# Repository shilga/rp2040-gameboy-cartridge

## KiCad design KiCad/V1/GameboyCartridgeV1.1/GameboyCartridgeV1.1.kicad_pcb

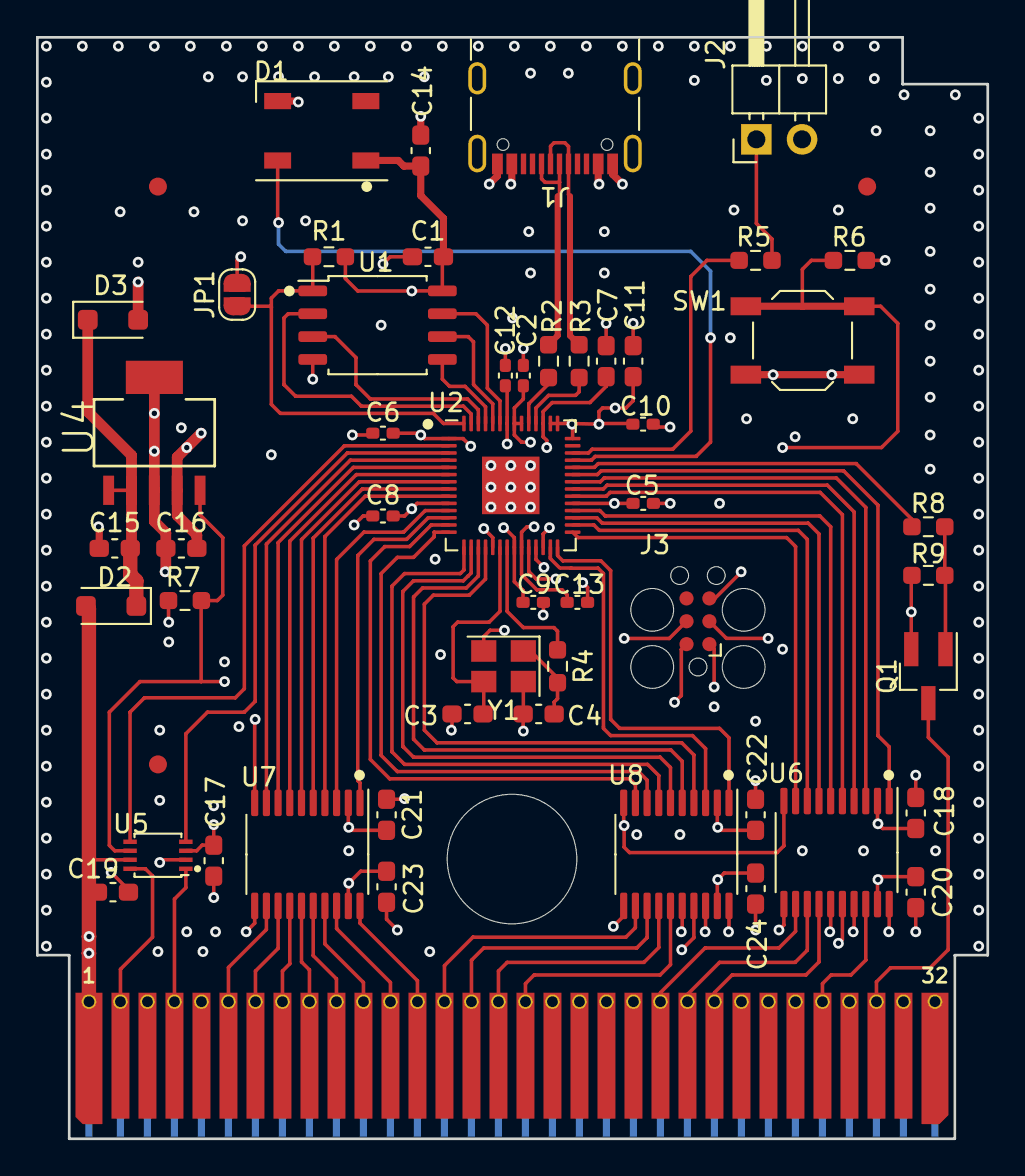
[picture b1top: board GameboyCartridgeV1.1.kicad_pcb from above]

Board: 4 copper layers, 52.8 x 61.2 mm, 54 parts (0 on the bottom side), 81 nets.

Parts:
C1, C14, C17, C18, C19, C20, C21, C22, C23, C24: 100nF; C_0603_1608Metric_Pad1.08x0.95mm_HandSolder
C2, C5, C6, C8, C9, C10, C12, C13: 100nF; C_0402_1005Metric_Pad0.74x0.62mm_HandSolder
C3, C4: 15pF; C_0603_1608Metric_Pad1.08x0.95mm_HandSolder
C7, C11: 2.2uF; C_0603_1608Metric_Pad1.08x0.95mm_HandSolder
C15: 4.7uF; C_0603_1608Metric_Pad1.08x0.95mm_HandSolder
C16: 10uF; C_0603_1608Metric_Pad1.08x0.95mm_HandSolder
D1: WS2812B; LED_WS2812B_PLCC4_5.0x5.0mm_P3.2mm
D2, D3: D_Schottky; D_SOD-123F
FID1, FID2, FID3: Fiducial; Fiducial_1mm_Mask2mm
J1: USB_C_Receptacle_USB2.0; USB_C_Receptacle_GCT_USB4105-xx-A_16P_TopMnt_Horizontal
J2: DBG_UART; PinHeader_1x02_P2.54mm_Horizontal
J3: Conn_01x06; Tag-Connect_TC2030-IDC-FP_2x03_P1.27mm_Vertical
JP1: USB_BOOT_SEL; SolderJumper-2_P1.3mm_Open_RoundedPad1.0x1.5mm
Q1: CJ2302; SOT-23_Handsoldering
R1, R6: 10k; R_0603_1608Metric_Pad0.98x0.95mm_HandSolder
R2, R3: 27R; R_0603_1608Metric_Pad0.98x0.95mm_HandSolder
R4, R8: 1k; R_0603_1608Metric_Pad0.98x0.95mm_HandSolder
R5: 10R; R_0603_1608Metric_Pad0.98x0.95mm_HandSolder
R7, R9: 470k; R_0603_1608Metric_Pad0.98x0.95mm_HandSolder
SW1: SW_Push; SW_SPST_TL3342
U1: W25Q128JVS; SOIC-8_5.23x5.23mm_P1.27mm
U2: RP2040; QFN-56-1EP_7x7mm_P0.4mm_EP3.2x3.2mm
U3: CartBus; GameBoy_Cartridge_EdgeConnector
U4: MCP1825T-3302E/DC; SOT230P700X180-6N
U5: TXB0102DCU; VSSOP-8_2.4x2.1mm_P0.5mm
U6, U7, U8: TXB0108PW; TSSOP-20_4.4x6.5mm_P0.65mm
Y1: 12MHz; Crystal_SMD_TXC_7M-4Pin_3.2x2.5mm

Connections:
+1V1: C7.2, C12.2, C13.2, U2.23 (DVDD), U2.45 (VREG_VOUT), U2.50 (DVDD)
+3V3: C1.2, C2.2, C5.2, C6.2, C8.2, C9.2, C10.2, C11.2, C14.2, C16.2, C17.2, C18.2, C21.2, C22.2, D1.1 (VDD), J3.1, R1.2, R6.2, R7.2, U1.8 (VCC), U2.1 (IOVDD), U2.10 (IOVDD), U2.22 (IOVDD), U2.33 (IOVDD), U2.42 (IOVDD), U2.43 (ADC_AVDD), U2.44 (VREG_IN), U2.48 (USB_VDD), U2.49 (IOVDD), U4.4 (VOUT), U5.3 (VCCA), U6.2 (VCCA), U7.2 (VCCA), U8.2 (VCCA)
+5V: C15.2, D2.1 (K), D3.1 (K), U4.1 (*SHDN), U4.2 (VIN)
ADDR_BUS0: U2.4 (GPIO2), U7.9 (A8)
ADDR_BUS1: U2.5 (GPIO3), U7.8 (A7)
ADDR_BUS2: U2.6 (GPIO4), U7.7 (A6)
ADDR_BUS3: U2.7 (GPIO5), U7.6 (A5)
ADDR_BUS4: U2.8 (GPIO6), U7.5 (A4)
ADDR_BUS5: U2.9 (GPIO7), U7.4 (A3)
ADDR_BUS6: U2.11 (GPIO8), U7.3 (A2)
ADDR_BUS7: U2.12 (GPIO9), U7.1 (A1)
ADDR_BUS8: U2.13 (GPIO10), U8.9 (A8)
ADDR_BUS9: U2.14 (GPIO11), U8.8 (A7)
ADDR_BUS10: U2.15 (GPIO12), U8.7 (A6)
ADDR_BUS11: U2.16 (GPIO13), U8.6 (A5)
ADDR_BUS12: U2.17 (GPIO14), U8.5 (A4)
ADDR_BUS13: U2.18 (GPIO15), U8.4 (A3)
ADDR_BUS14: U2.27 (GPIO16), U8.3 (A2)
ADDR_BUS15: U2.28 (GPIO17), U8.1 (A1)
BUS_CLK: U2.2 (GPIO0), U5.5 (A1)
BUS_RD: U2.3 (GPIO1), U5.4 (A2)
BUS_RST: R8.2, U2.38 (GPIO26_ADC0)
DATA_BUS0: U2.29 (GPIO18), U6.9 (A8)
DATA_BUS1: U2.30 (GPIO19), U6.8 (A7)
DATA_BUS2: U2.31 (GPIO20), U6.7 (A6)
DATA_BUS3: U2.32 (GPIO21), U6.6 (A5)
DATA_BUS4: U2.34 (GPIO22), U6.5 (A4)
DATA_BUS5: U2.35 (GPIO23), U6.4 (A3)
DATA_BUS6: U2.36 (GPIO24), U6.3 (A2)
DATA_BUS7: U2.37 (GPIO25), U6.1 (A1)
DEBUG_UART_TX: R5.1, U2.40 (GPIO28_ADC2)
GB_A0: U3.6 (A0), U7.12 (B8)
GB_A1: U3.7 (A1), U7.13 (B7)
GB_A2: U3.8 (A2), U7.14 (B6)
GB_A3: U3.9 (A3), U7.15 (B5)
GB_A4: U3.10 (A4), U7.16 (B4)
GB_A5: U3.11 (A5), U7.17 (B3)
GB_A6: U3.12 (A6), U7.18 (B2)
GB_A7: U3.13 (A7), U7.20 (B1)
GB_A8: U3.14 (A8), U8.12 (B8)
GB_A9: U3.15 (A9), U8.13 (B7)
GB_A10: U3.16 (A10), U8.14 (B6)
GB_A11: U3.17 (A11), U8.15 (B5)
GB_A12: U3.18 (A12), U8.16 (B4)
GB_A13: U3.19 (A13), U8.17 (B3)
GB_A14: U3.20 (A14), U8.18 (B2)
GB_A15: U3.21 (A15), U8.20 (B1)
GB_CLK: U3.2 (CLK~), U5.8 (B1)
GB_D0: U3.22 (D0), U6.12 (B8)
GB_D1: U3.23 (D1), U6.13 (B7)
GB_D2: U3.24 (D2), U6.14 (B6)
GB_D3: U3.25 (D3), U6.15 (B5)
GB_D4: U3.26 (D4), U6.16 (B4)
GB_D5: U3.27 (D5), U6.17 (B3)
GB_D6: U3.28 (D6), U6.18 (B2)
GB_D7: U3.29 (D7), U6.20 (B1)
GB_RD: U3.4 (RD), U5.1 (B2)
GB_RST: Q1.3 (D), U3.30 (RST)
GND: C1.1, C2.1, C3.1, C4.1, C5.1, C6.1, C7.1, C8.1, C9.1, C10.1, C11.1, C12.1, C13.1, C14.1, C15.1, C16.1, C17.1, C18.1, C19.1, C20.1, C21.1, C22.1, C23.1, C24.1, D1.3 (VSS), J1.A1 (GND), J1.A12 (GND), J1.B1 (GND), J1.B12 (GND), J1.S1 (SHIELD), J2.2, J3.5, JP1.2 (B), Q1.2 (S), R9.2, SW1.2, U1.4 (GND), U2.19 (TESTEN), U2.57 (GND), U3.32 (GND), U4.3 (GND_(TAB)), U4.6 (GND_(TAB)_2), U5.2 (GND), U6.11 (GND), U7.11 (GND), U8.11 (GND), Y1.2, Y1.4
LED_DIN: D1.4 (DIN), U2.39 (GPIO27_ADC1)
unnamed: C4.2, R4.2, Y1.1
unnamed: J2.1, R5.2
unnamed: Q1.1 (G), R8.1, R9.1
unnamed: R3.1, U2.46 (USB_DM)
unnamed: R2.1, U2.47 (USB_DP)
unnamed: C3.2, U2.20 (XIN), Y1.3
unnamed: R4.1, U2.21 (XOUT)
POWER_GOOD: R7.1, U4.5 (PWRGD), U5.6 (OE), U6.10 (OE), U7.10 (OE), U8.10 (OE)
QSPI_SCLK: U1.6 (CLK), U2.52 (QSPI_SCLK)
QSPI_SD0: U1.5 (DI(IO0)), U2.53 (QSPI_SD0)
QSPI_SD1: U1.2 (DO(IO1)), U2.55 (QSPI_SD1)
QSPI_SD2: U1.3 (IO2), U2.54 (QSPI_SD2)
QSPI_SD3: U1.7 (IO3), U2.51 (QSPI_SD3)
QSPI_SS: JP1.1 (A), R1.1, U1.1 (~CS), U2.56 (QSPI_SS)
RST: J3.3, R6.1, SW1.1, U2.26 (RUN)
SWCLK: J3.4, U2.24 (SWCLK)
SWDIO: J3.2, U2.25 (SWD)
USB_D+: J1.A6 (D+), J1.B6 (D+), R2.2
USB_D-: J1.A7 (D-), J1.B7 (D-), R3.2
VBUS: D3.2 (A), J1.A4 (VBUS), J1.A9 (VBUS), J1.B4 (VBUS), J1.B9 (VBUS)
VCC: C19.2, C20.2, C23.2, C24.2, D2.2 (A), U3.1 (VCC), U5.7 (VCCB), U6.19 (VCCB), U7.19 (VCCB), U8.19 (VCCB)

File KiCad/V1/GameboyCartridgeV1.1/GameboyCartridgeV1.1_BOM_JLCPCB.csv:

Comment,Designator,Footprint,LCSC
"100nF","C1,C14,C17,C18,C19,C20,C21,C22,C23,C24","Capacitor_SMD:C_0603_1608Metric_Pad1.08x0.95mm_HandSolder",""
"4.7uF","C15","Capacitor_SMD:C_0603_1608Metric_Pad1.08x0.95mm_HandSolder",""
"10uF","C16","Capacitor_SMD:C_0603_1608Metric_Pad1.08x0.95mm_HandSolder",""
"100nF","C2,C5,C6,C8,C9,C10,C12,C13","Capacitor_SMD:C_0402_1005Metric_Pad0.74x0.62mm_HandSolder",""
"15pF","C3,C4","Capacitor_SMD:C_0603_1608Metric_Pad1.08x0.95mm_HandSolder","C1644"
"2.2uF","C7,C11","Capacitor_SMD:C_0603_1608Metric_Pad1.08x0.95mm_HandSolder",""
"WS2812B","D1","LED_SMD:LED_WS2812B_PLCC4_5.0x5.0mm_P3.2mm","C2761795"
"D_Schottky","D2,D3","Diode_SMD:D_SOD-123F","C669022"
"USB_C_Receptacle_USB2.0","J1","Connector_USB:USB_C_Receptacle_GCT_USB4105-xx-A_16P_TopMnt_Horizontal","C2927037"
"CJ2302","Q1","Package_TO_SOT_SMD:SOT-23_Handsoldering","C8548"
"10k","R1,R6","Resistor_SMD:R_0603_1608Metric_Pad0.98x0.95mm_HandSolder",""
"27R","R2,R3","Resistor_SMD:R_0603_1608Metric_Pad0.98x0.95mm_HandSolder",""
"1k","R4,R8","Resistor_SMD:R_0603_1608Metric_Pad0.98x0.95mm_HandSolder",""
"10R","R5","Resistor_SMD:R_0603_1608Metric_Pad0.98x0.95mm_HandSolder",""
"470k","R7,R9","Resistor_SMD:R_0603_1608Metric_Pad0.98x0.95mm_HandSolder",""
"SW_Push","SW1","Button_Switch_SMD:SW_SPST_TL3342","C2886898"
"W25Q128JVS","U1","Package_SO:SOIC-8_5.23x5.23mm_P1.27mm","C97521"
"RP2040","U2","Package_DFN_QFN:QFN-56-1EP_7x7mm_P0.4mm_EP3.2x3.2mm","C2040"
"MCP1825T-3302E/DC","U4","SnapEDA:SOT230P700X180-6N","C632684"
"TXB0102DCU","U5","Package_SO:VSSOP-8_2.4x2.1mm_P0.5mm","C60709"
"TXB0108PW","U6,U7,U8","Package_SO:TSSOP-20_4.4x6.5mm_P0.65mm","C53406"
"12MHz","Y1","Crystal:Crystal_SMD_TXC_7M-4Pin_3.2x2.5mm","C668845"

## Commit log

2023-11-11 Change folder structure
    - Fix Library paths
    - Add Libraries
    - Add Gerbers, BOM, Position file compatible with JLPCB
